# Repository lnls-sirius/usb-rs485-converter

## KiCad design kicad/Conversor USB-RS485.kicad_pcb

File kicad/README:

Adjust hole of Mini-USB B
Delete route for LPKF around Sirius logo

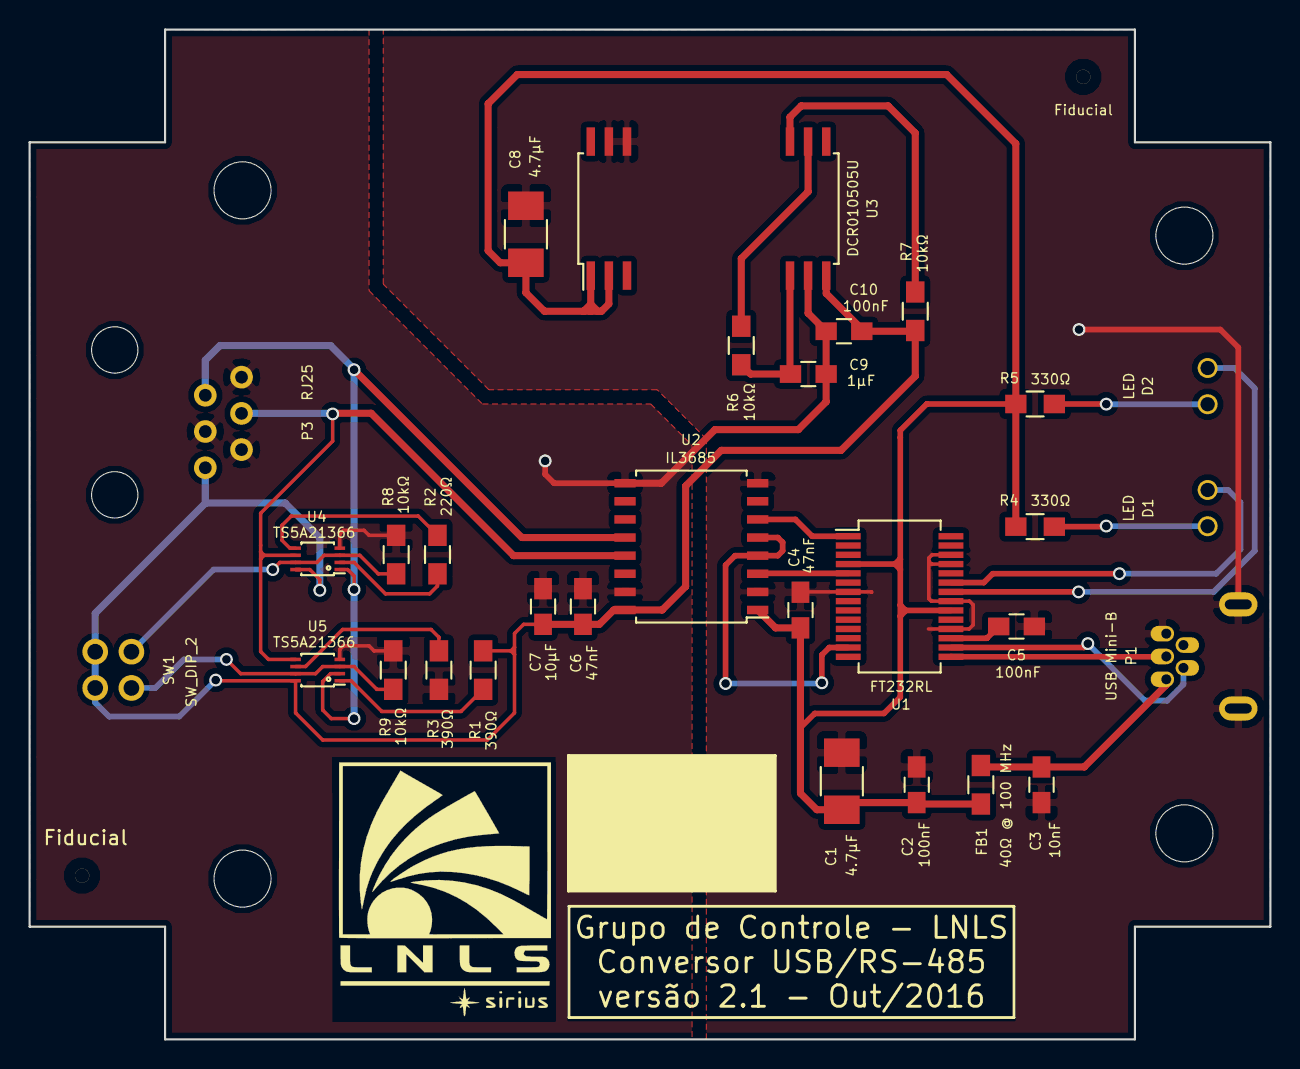
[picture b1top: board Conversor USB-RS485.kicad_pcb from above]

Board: 2 copper layers, 87.0 x 70.8 mm, 36 parts (0 on the bottom side), 26 nets.

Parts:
C1, C8: 4.7µF; C_1210_HandSoldering
C2, C5, C10: 100nF; C_0805_HandSoldering
C3: 10nF; C_0805_HandSoldering
C4, C6: 47nF; C_0805_HandSoldering
C7: 10µF; C_0805_HandSoldering
C9: 1µF; C_0805_HandSoldering
D1, D2: LED; LED_para_painel_KINGBRIGHT
F1, F2, F3, F4: Furo de fixação (4mm); MountingHole_4mm
FB1: 40Ω @ 100 MHz; R_0805_HandSoldering
Fiducial: Fiducial_1mm_Dia_2.54mm_Outer_CopperTop
Fiducial#2: Fiducial_1mm_Dia_2.54mm_Outer_CopperBottom
P1: USB Mini-B; USB_Mini-B
P3: RJ25
R1, R3: 390Ω; R_0805_HandSoldering
R2: 220Ω; R_0805_HandSoldering
R4, R5: 330Ω; R_0805_HandSoldering
R6, R7, R8, R9: 10kΩ; R_0805_HandSoldering
SW1: SW_DIP_2; DIP_switch_(2_positions)
U1: FT232RL; SSOP-28_5.3x10.2mm_Pitch0.65mm
U2: IL3685; SOIC-16_7.5x10.3mm_Pitch1.27mm
U3: DCR010505U
U4, U5: TS5A21366; VSSOP-8

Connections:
+5V: C1.1, C2.1, C4.1, C8.1, FB1.1, R4.1, R5.1, U1.4, U1.20, U2.1, U3.1, U3.2
/5V_ISOLATED: C6.1, C7.1, C10.1, P3.6, R1.2, R7.1, SW1.1, SW1.3, U2.16, U3.14, U4.8, U5.8
/GND_ISOLATED: C6.2, C7.2, C9.2, C10.2, P3.1, P3.4, P3.5, R3.2, R8.1, R9.1, U2.9, U2.15, U3.13, U4.4, U5.4
/RS485+: P3.2, U2.12, U4.1, U5.2
/RS485-: P3.3, U2.13, U4.6, U5.5
/RXD: U1.5, U2.3
/RXLED#: D2.1, U1.22
/TXD: U1.1, U2.6
/TXDEN: U1.13, U2.4, U2.5
/TXLED#: D1.1, U1.23
/USB_D+: P1.3, U1.15
/USB_D-: P1.2, U1.16
GND: C1.2, C2.2, C3.2, C4.2, C5.2, C8.2, P1.5, P1.6, P1.7, U1.7, U1.18, U1.21, U1.25, U1.26, U2.2, U2.8, U3.26, U3.27
unnamed: C3.1, FB1.2, P1.1
unnamed: C5.1, U1.17
unnamed: C9.1, R6.1, U3.12
unnamed: D1.2, R4.2
unnamed: D2.2, R5.2
unnamed: R1.1, U5.1
unnamed: R2.1, U4.2
unnamed: R2.2, U4.5
unnamed: R3.1, U5.6
unnamed: R6.2, U3.16
unnamed: R7.2, U3.17
unnamed: R8.2, SW1.4, U4.3, U4.7
unnamed: R9.2, SW1.2, U5.3, U5.7

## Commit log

2019-04-09 repo migrated from CNPEM in-house GitLab
